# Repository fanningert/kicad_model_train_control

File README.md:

# Model Train Control

Control unit for analog model trains, based on ESPHome. A Home Assistant instance is used for visualization and control. This board is stackable up to 64 boards and every board has 16 outputs (3 pin). The Voltage is limited on the outputs per ESPHome template.
It comes in three variants, but all variants are the same boards. Only some components are not placed.

* Primary node with ESP32-S3-Wroom-2
* Primary node with ESP32-Devkit (can also be used as sub node with 3,3V power supply and protection)
* Sub node

## Features

* 16 h-bridges per board and stackable to 64 boards
* Reverse Voltage, Over Voltage and Under Voltage protection
* (optional) ESP32-Devkit
* (optional) ESP32-S3-Wroom-2

## Simple graphic of the board connections

```mermaid
flowchart LR
    Z[PowerSupply] ===|24V DC| A
    A[PCB_Core1] ===|24V DC, 3.3V, I2C| B & C & D
    B[PCB_Core2]
    C[PCB_Core...]
    D[PCB_Core64]
```

## Supported szenarios

- Power line
- Yield
- Generic Switch
- Signal
- Uncoupler

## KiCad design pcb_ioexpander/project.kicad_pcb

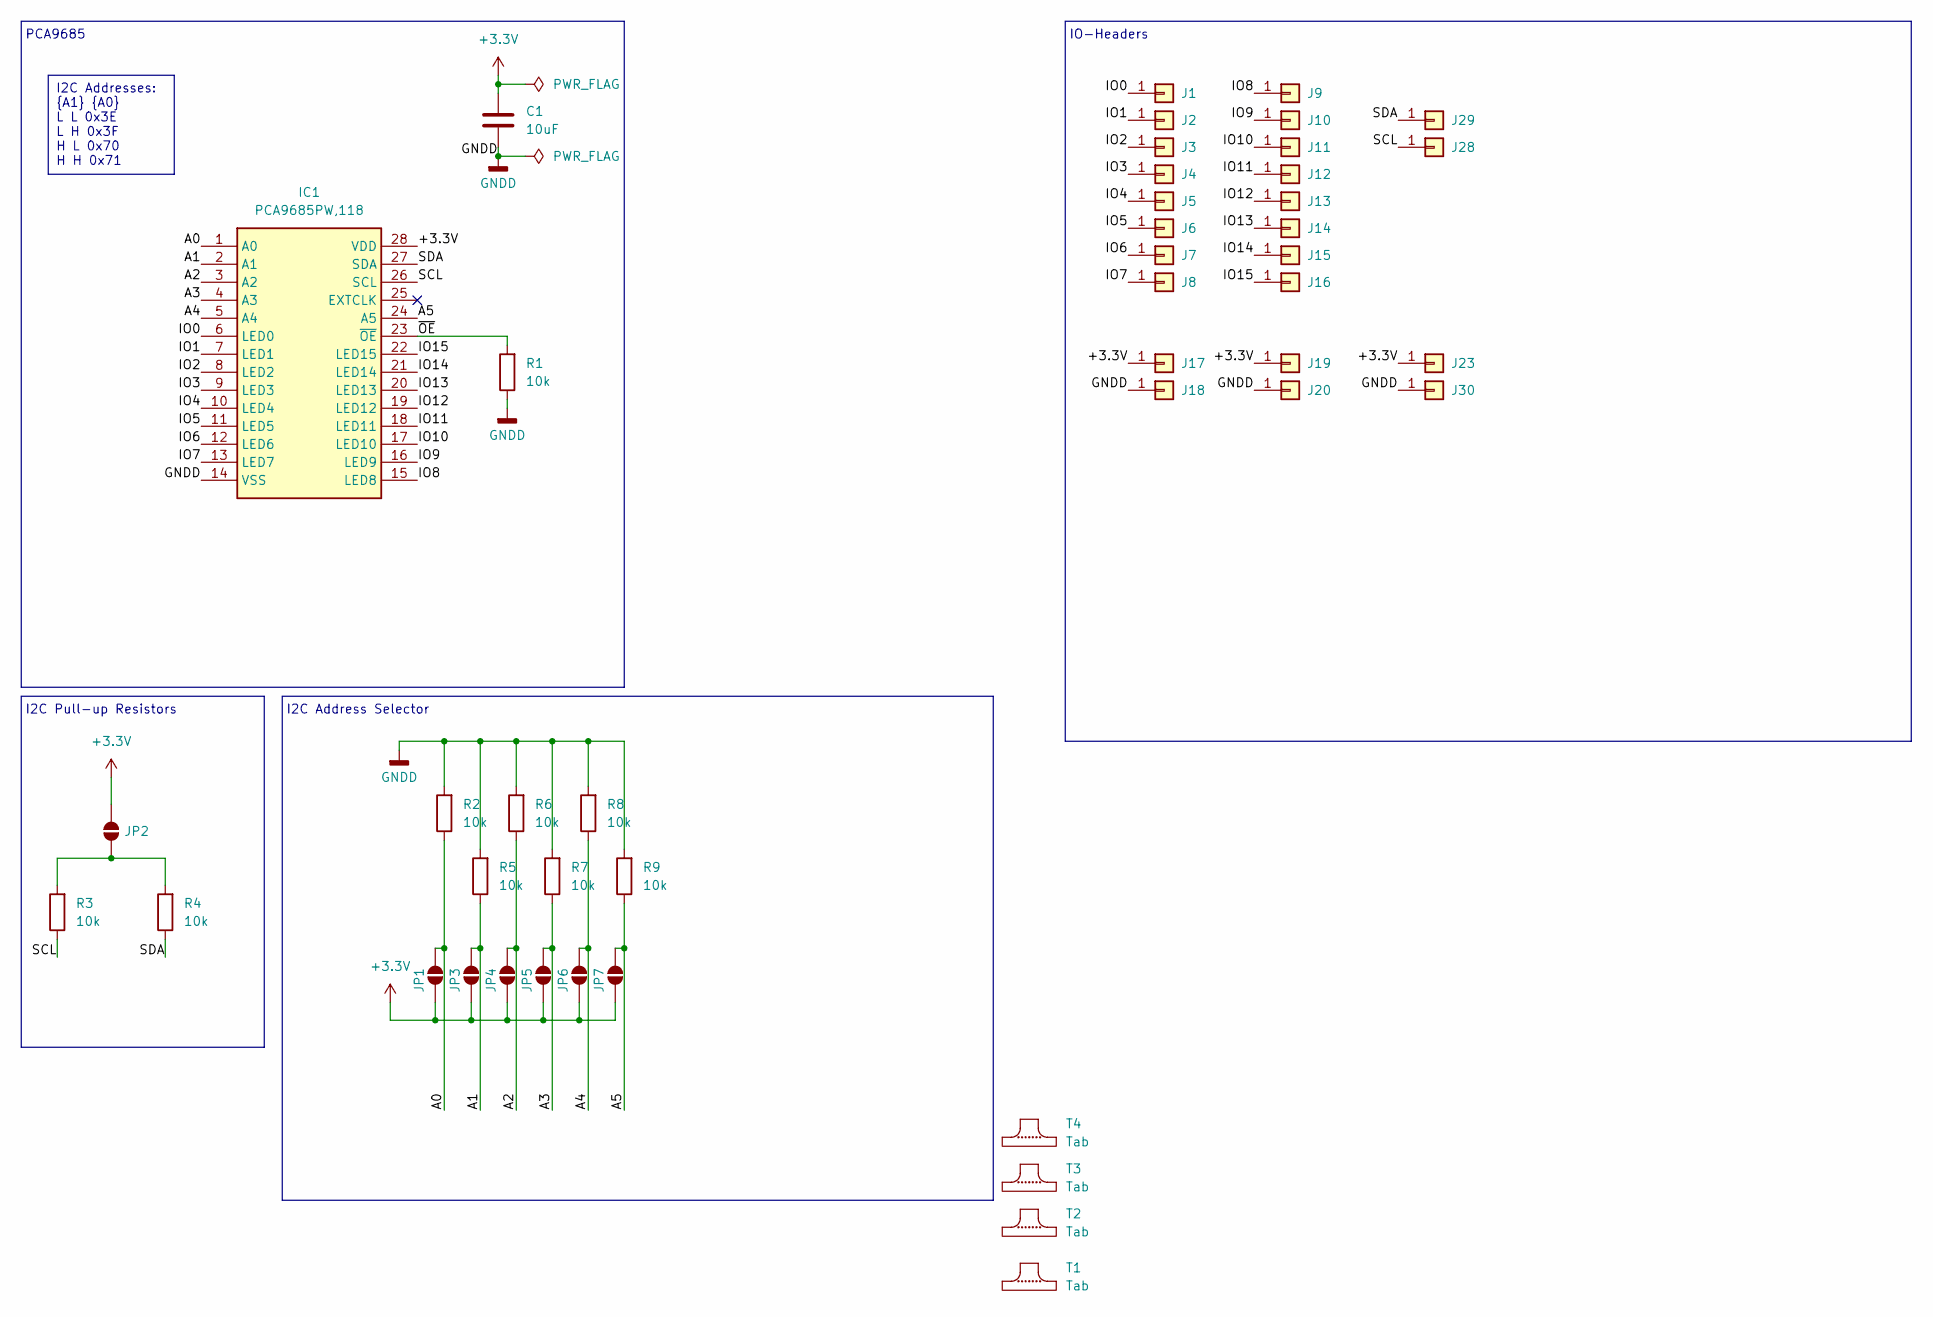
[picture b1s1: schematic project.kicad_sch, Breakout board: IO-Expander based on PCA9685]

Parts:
C1: 10uF; C_0402_1005Metric_Pad0.74x0.62mm_HandSolder
IC1: PCA9685PW,118; SOP65P640X110-28N; Mouser Part Number 771-PCA9685PW,118
J1, J2, J3, J4, J5, J6, J7, J8, J9, J10, J11, J12, J13, J14, J15, J16, J17, J18, J19, J20, J23, J28, J29, J30: Castellated_Hole02
JP1, JP2, JP3, JP4, JP5, JP6, JP7: SolderJumper_2_Open; SolderJumper-2_P1.3mm_Open_TrianglePad1.0x1.5mm
R1, R2, R3, R4, R5, R6, R7, R8, R9: 10k; R_0402_1005Metric_Pad0.72x0.64mm_HandSolder
T1, T2, T3, T4: Tab

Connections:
+3.3V: C1.1, IC1.28 (VDD), J17.1, J19.1, J23.1, JP1.2 (B), JP2.2 (B), JP3.2 (B), JP4.2 (B), JP5.2 (B), JP6.2 (B), JP7.2 (B)
/A0: IC1.1 (A0), JP1.1 (A), R2.1
/A1: IC1.2 (A1), JP3.1 (A), R5.1
/A2: IC1.3 (A2), JP4.1 (A), R6.1
/A3: IC1.4 (A3), JP5.1 (A), R7.1
/A4: IC1.5 (A4), JP6.1 (A), R8.1
/A5: IC1.24 (A5), JP7.1 (A), R9.1
/IO0: IC1.6 (LED0), J1.1
/IO1: IC1.7 (LED1), J2.1
/IO2: IC1.8 (LED2), J3.1
/IO3: IC1.9 (LED3), J4.1
/IO4: IC1.10 (LED4), J5.1
/IO5: IC1.11 (LED5), J6.1
/IO6: IC1.12 (LED6), J7.1
/IO7: IC1.13 (LED7), J8.1
/IO8: IC1.15 (LED8), J9.1
/IO9: IC1.16 (LED9), J10.1
/IO10: IC1.17 (LED10), J11.1
/IO11: IC1.18 (LED11), J12.1
/IO12: IC1.19 (LED12), J13.1
/IO13: IC1.20 (LED13), J14.1
/IO14: IC1.21 (LED14), J15.1
/IO15: IC1.22 (LED15), J16.1
/SCL: IC1.26 (SCL), J28.1, R3.1
/SDA: IC1.27 (SDA), J29.1, R4.1
/~OE: IC1.23 (~OE), R1.2
GNDD: C1.2, IC1.14 (VSS), J18.1, J20.1, J30.1, R1.1, R2.2, R5.2, R6.2, R7.2, R8.2, R9.2
unnamed: JP2.1 (A), R3.2, R4.2

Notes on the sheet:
I2C Addresses: {A1} {A0} L L 0x3E L H 0x3F H L 0x70 H H 0x71
IO-Headers
I2C Address Selector
I2C Pull-up Resistors
PCA9685

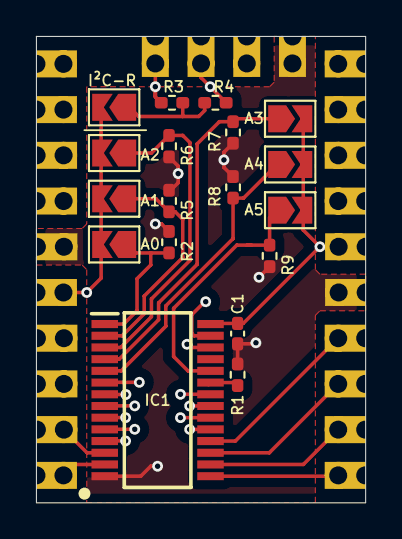
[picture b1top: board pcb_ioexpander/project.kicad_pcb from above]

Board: 4 copper layers, 18.3 x 25.9 mm, 47 parts (1 on the bottom side), 28 nets.

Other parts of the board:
QR*****: https://github.com/fanningert/kicad_pcb_ioexpander; //github.com/fanningert/kicad_pcb_ioexpander

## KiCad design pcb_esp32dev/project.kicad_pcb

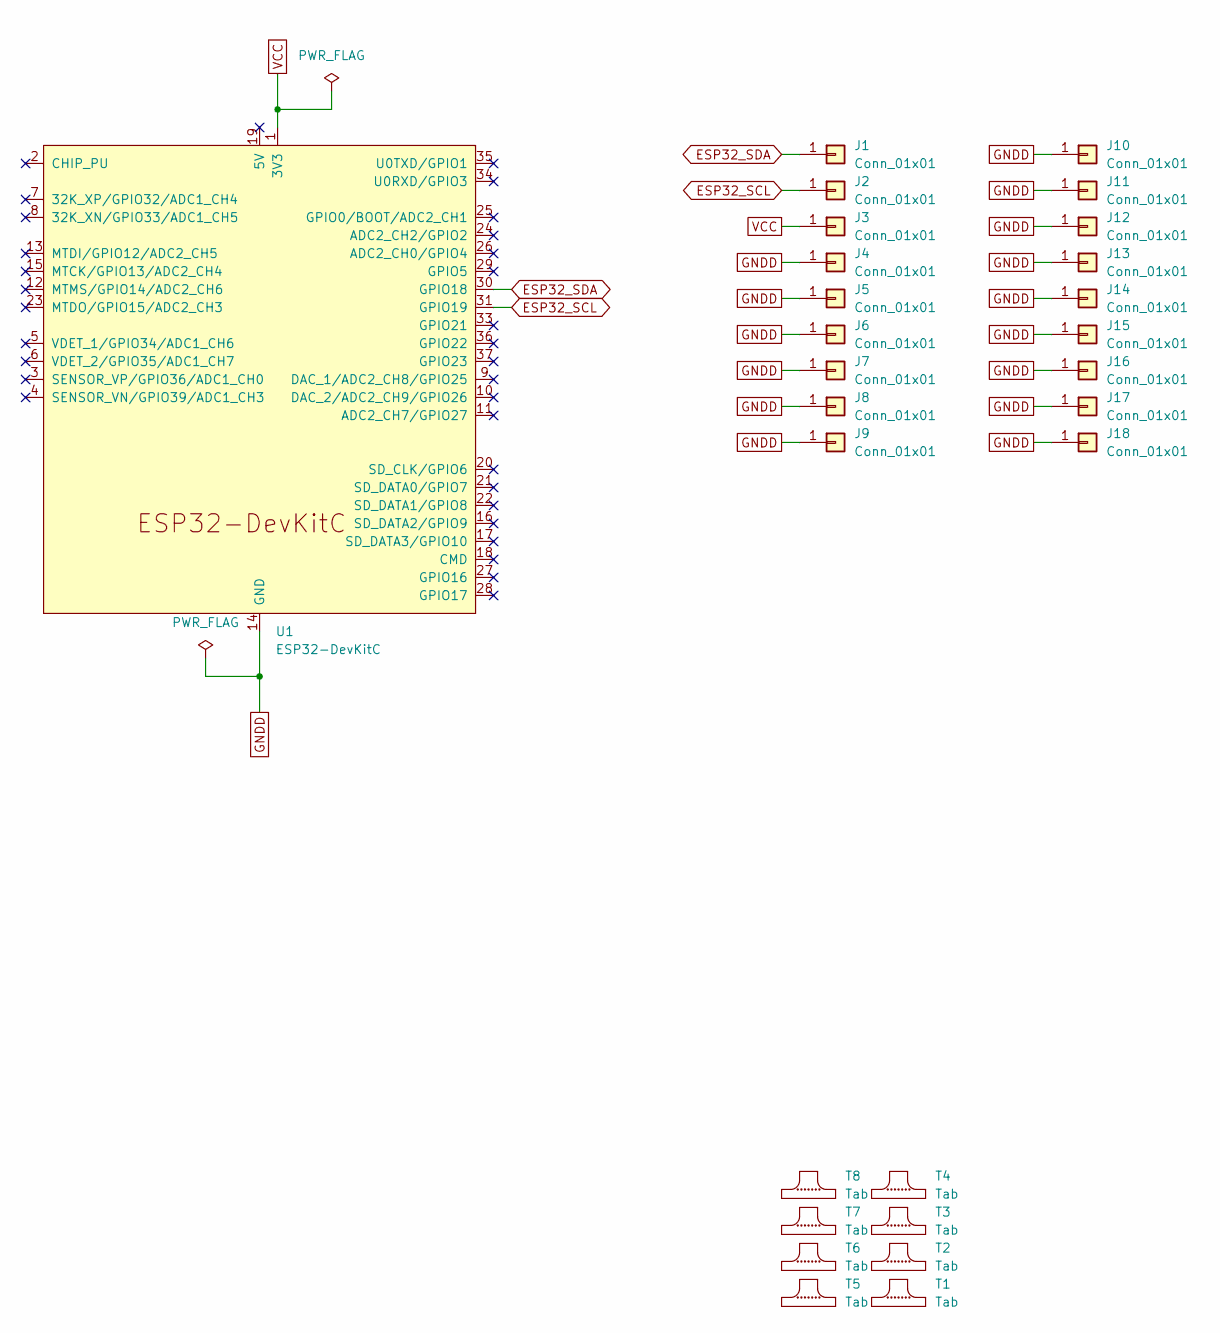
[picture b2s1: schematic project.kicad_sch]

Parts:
J1, J2, J3, J4, J5, J6, J7, J8, J9, J10, J11, J12, J13, J14, J15, J16, J17, J18: Conn_01x01; Castellated_Hole02
T1, T2, T3, T4, T5, T6, T7, T8: Tab
U1: ESP32-DevKitC

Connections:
ESP32_SCL: J2.1, U1.31 (GPIO19)
ESP32_SDA: J1.1, U1.30 (GPIO18)
GNDD: J4.1, J5.1, J6.1, J7.1, J8.1, J9.1, J10.1, J11.1, J12.1, J13.1, J14.1, J15.1, J16.1, J17.1, J18.1, U1.14 (GND), U1.32 (GND), U1.38 (GND)
VCC: J3.1, U1.1 (3V3)

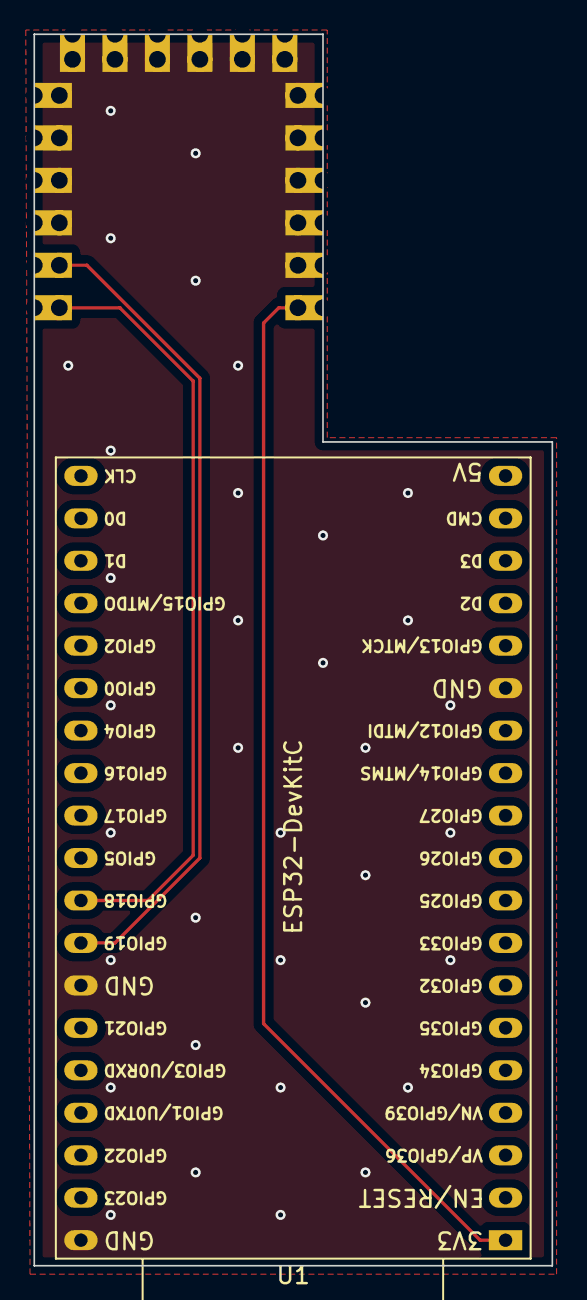
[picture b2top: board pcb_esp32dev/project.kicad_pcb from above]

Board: 2 copper layers, 31.0 x 73.7 mm, 27 parts (0 on the bottom side), 4 nets.

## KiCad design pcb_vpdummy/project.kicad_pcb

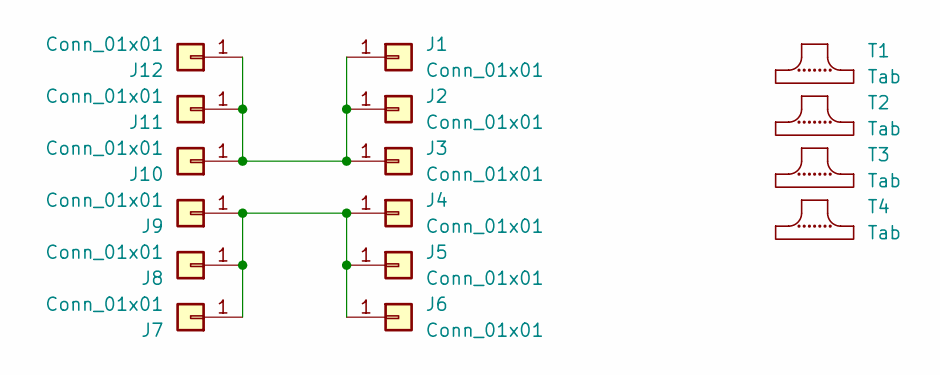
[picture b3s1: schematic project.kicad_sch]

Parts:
J1, J2, J3, J4, J5, J6, J7, J8, J9, J10, J11, J12: Conn_01x01; Castellated_Hole02
T1, T2, T3, T4: Tab

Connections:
unnamed: J1.1, J2.1, J3.1, J10.1, J11.1, J12.1
unnamed: J4.1, J5.1, J6.1, J7.1, J8.1, J9.1

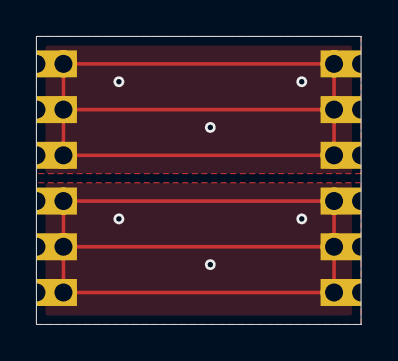
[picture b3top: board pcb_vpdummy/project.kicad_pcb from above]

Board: 2 copper layers, 18.0 x 16.0 mm, 16 parts (0 on the bottom side), 2 nets.

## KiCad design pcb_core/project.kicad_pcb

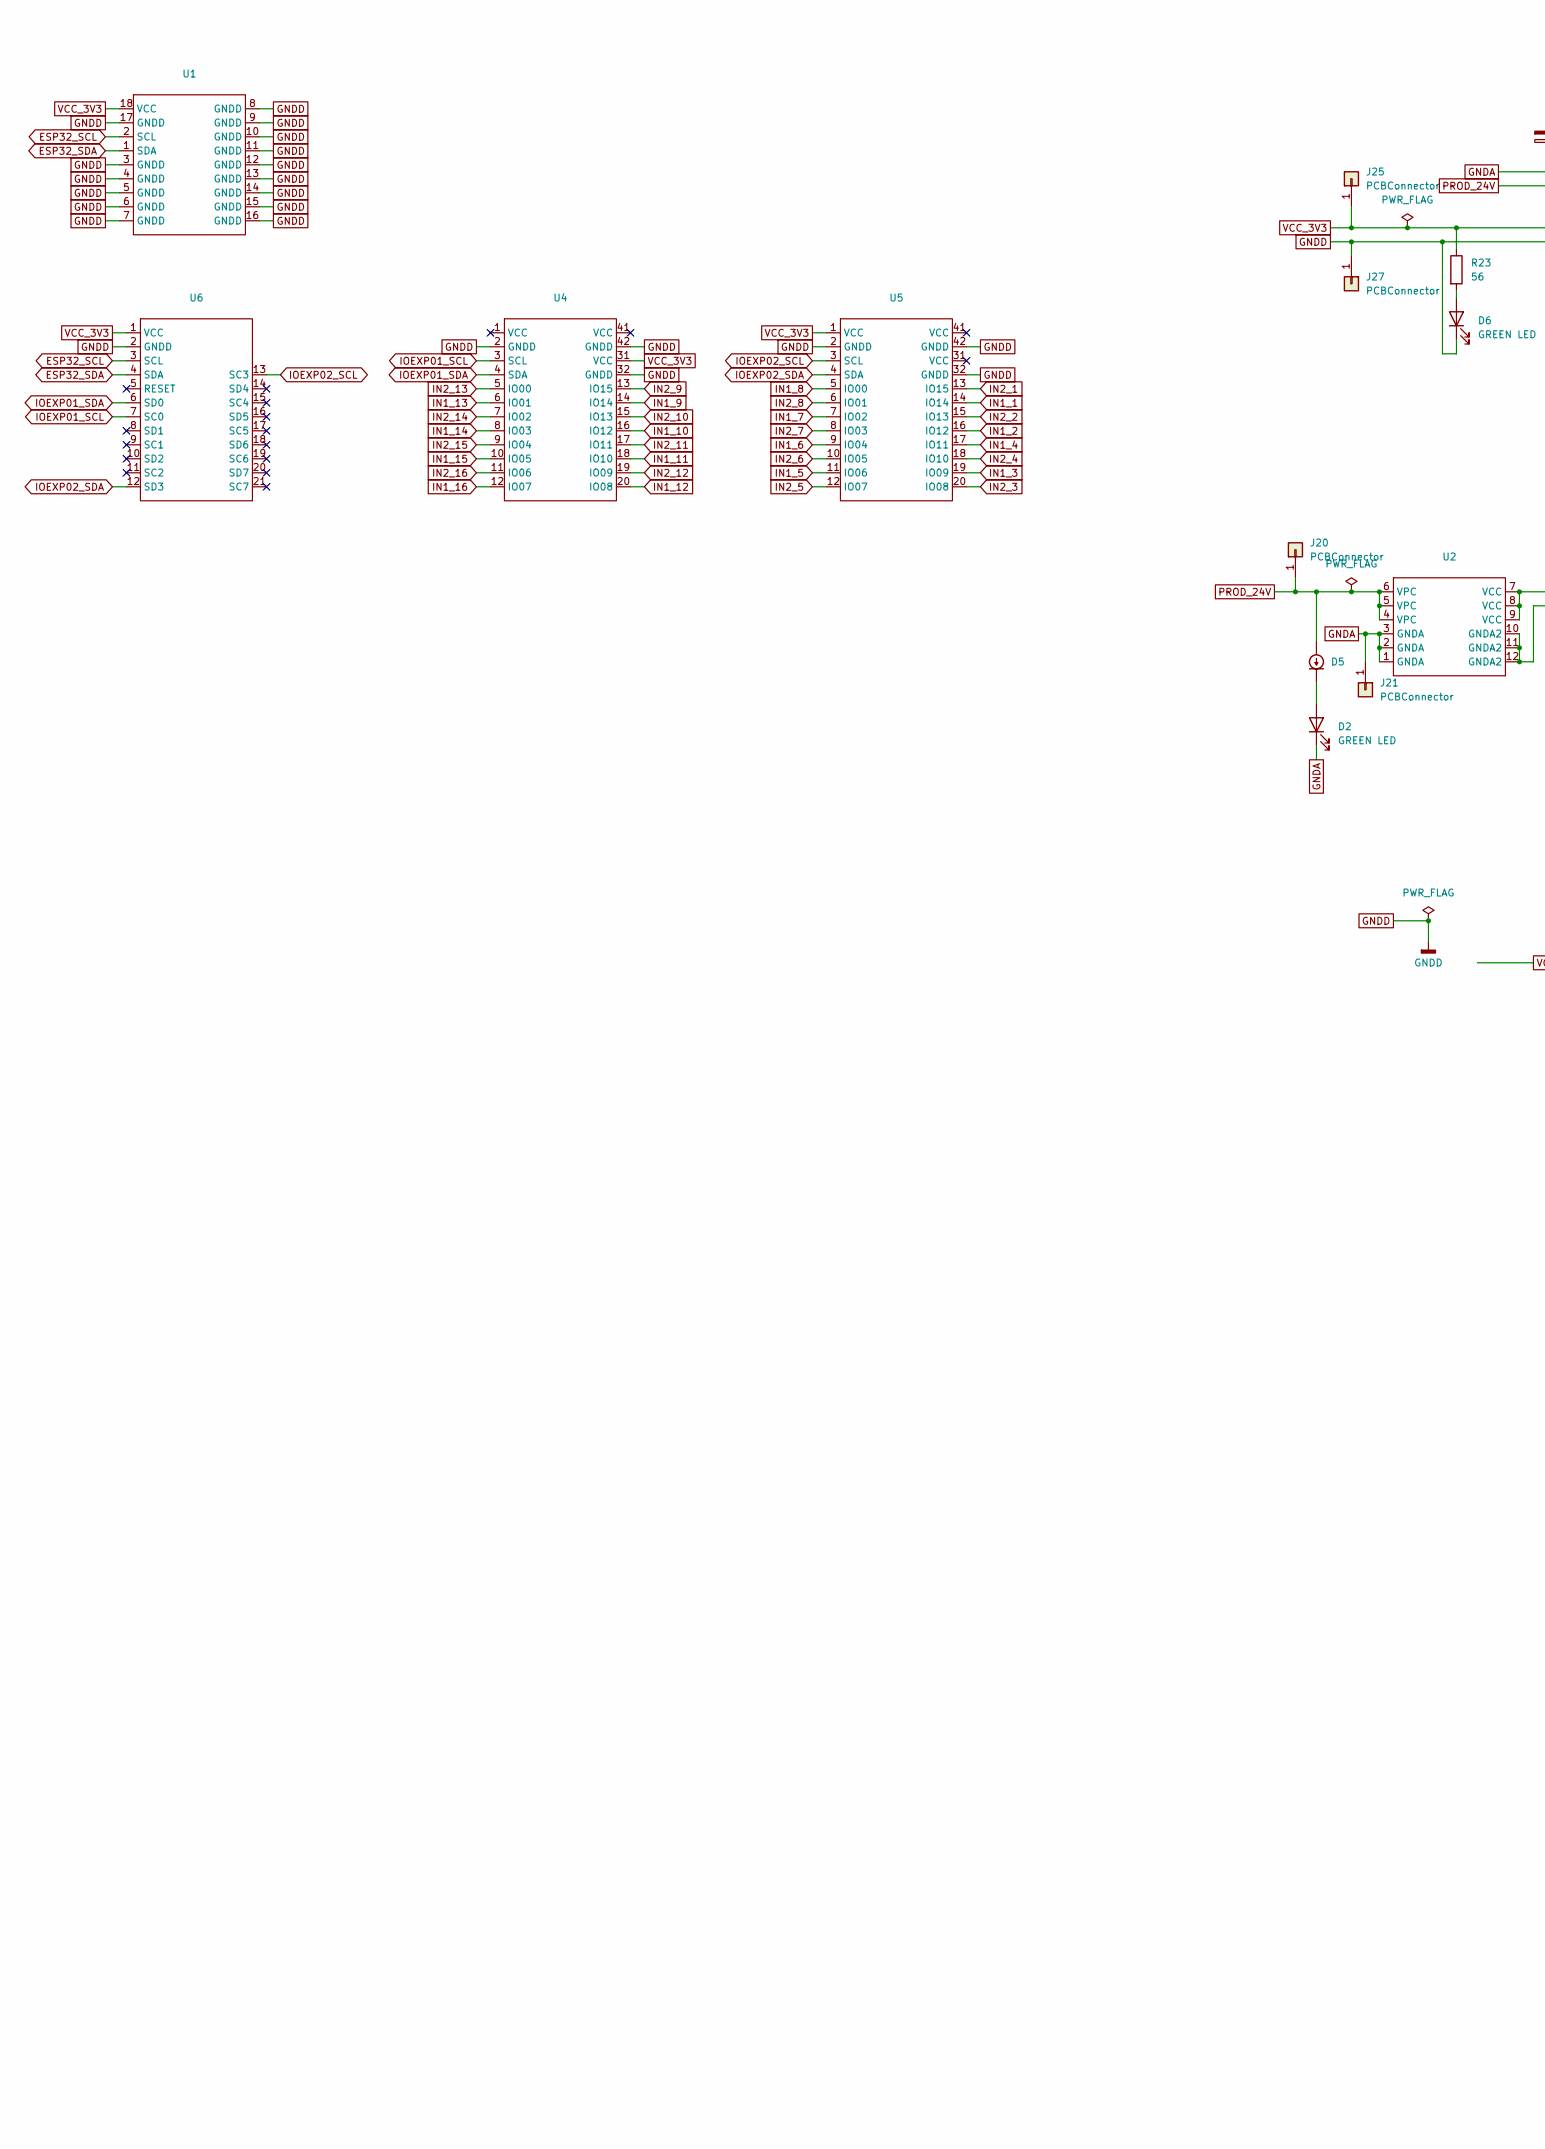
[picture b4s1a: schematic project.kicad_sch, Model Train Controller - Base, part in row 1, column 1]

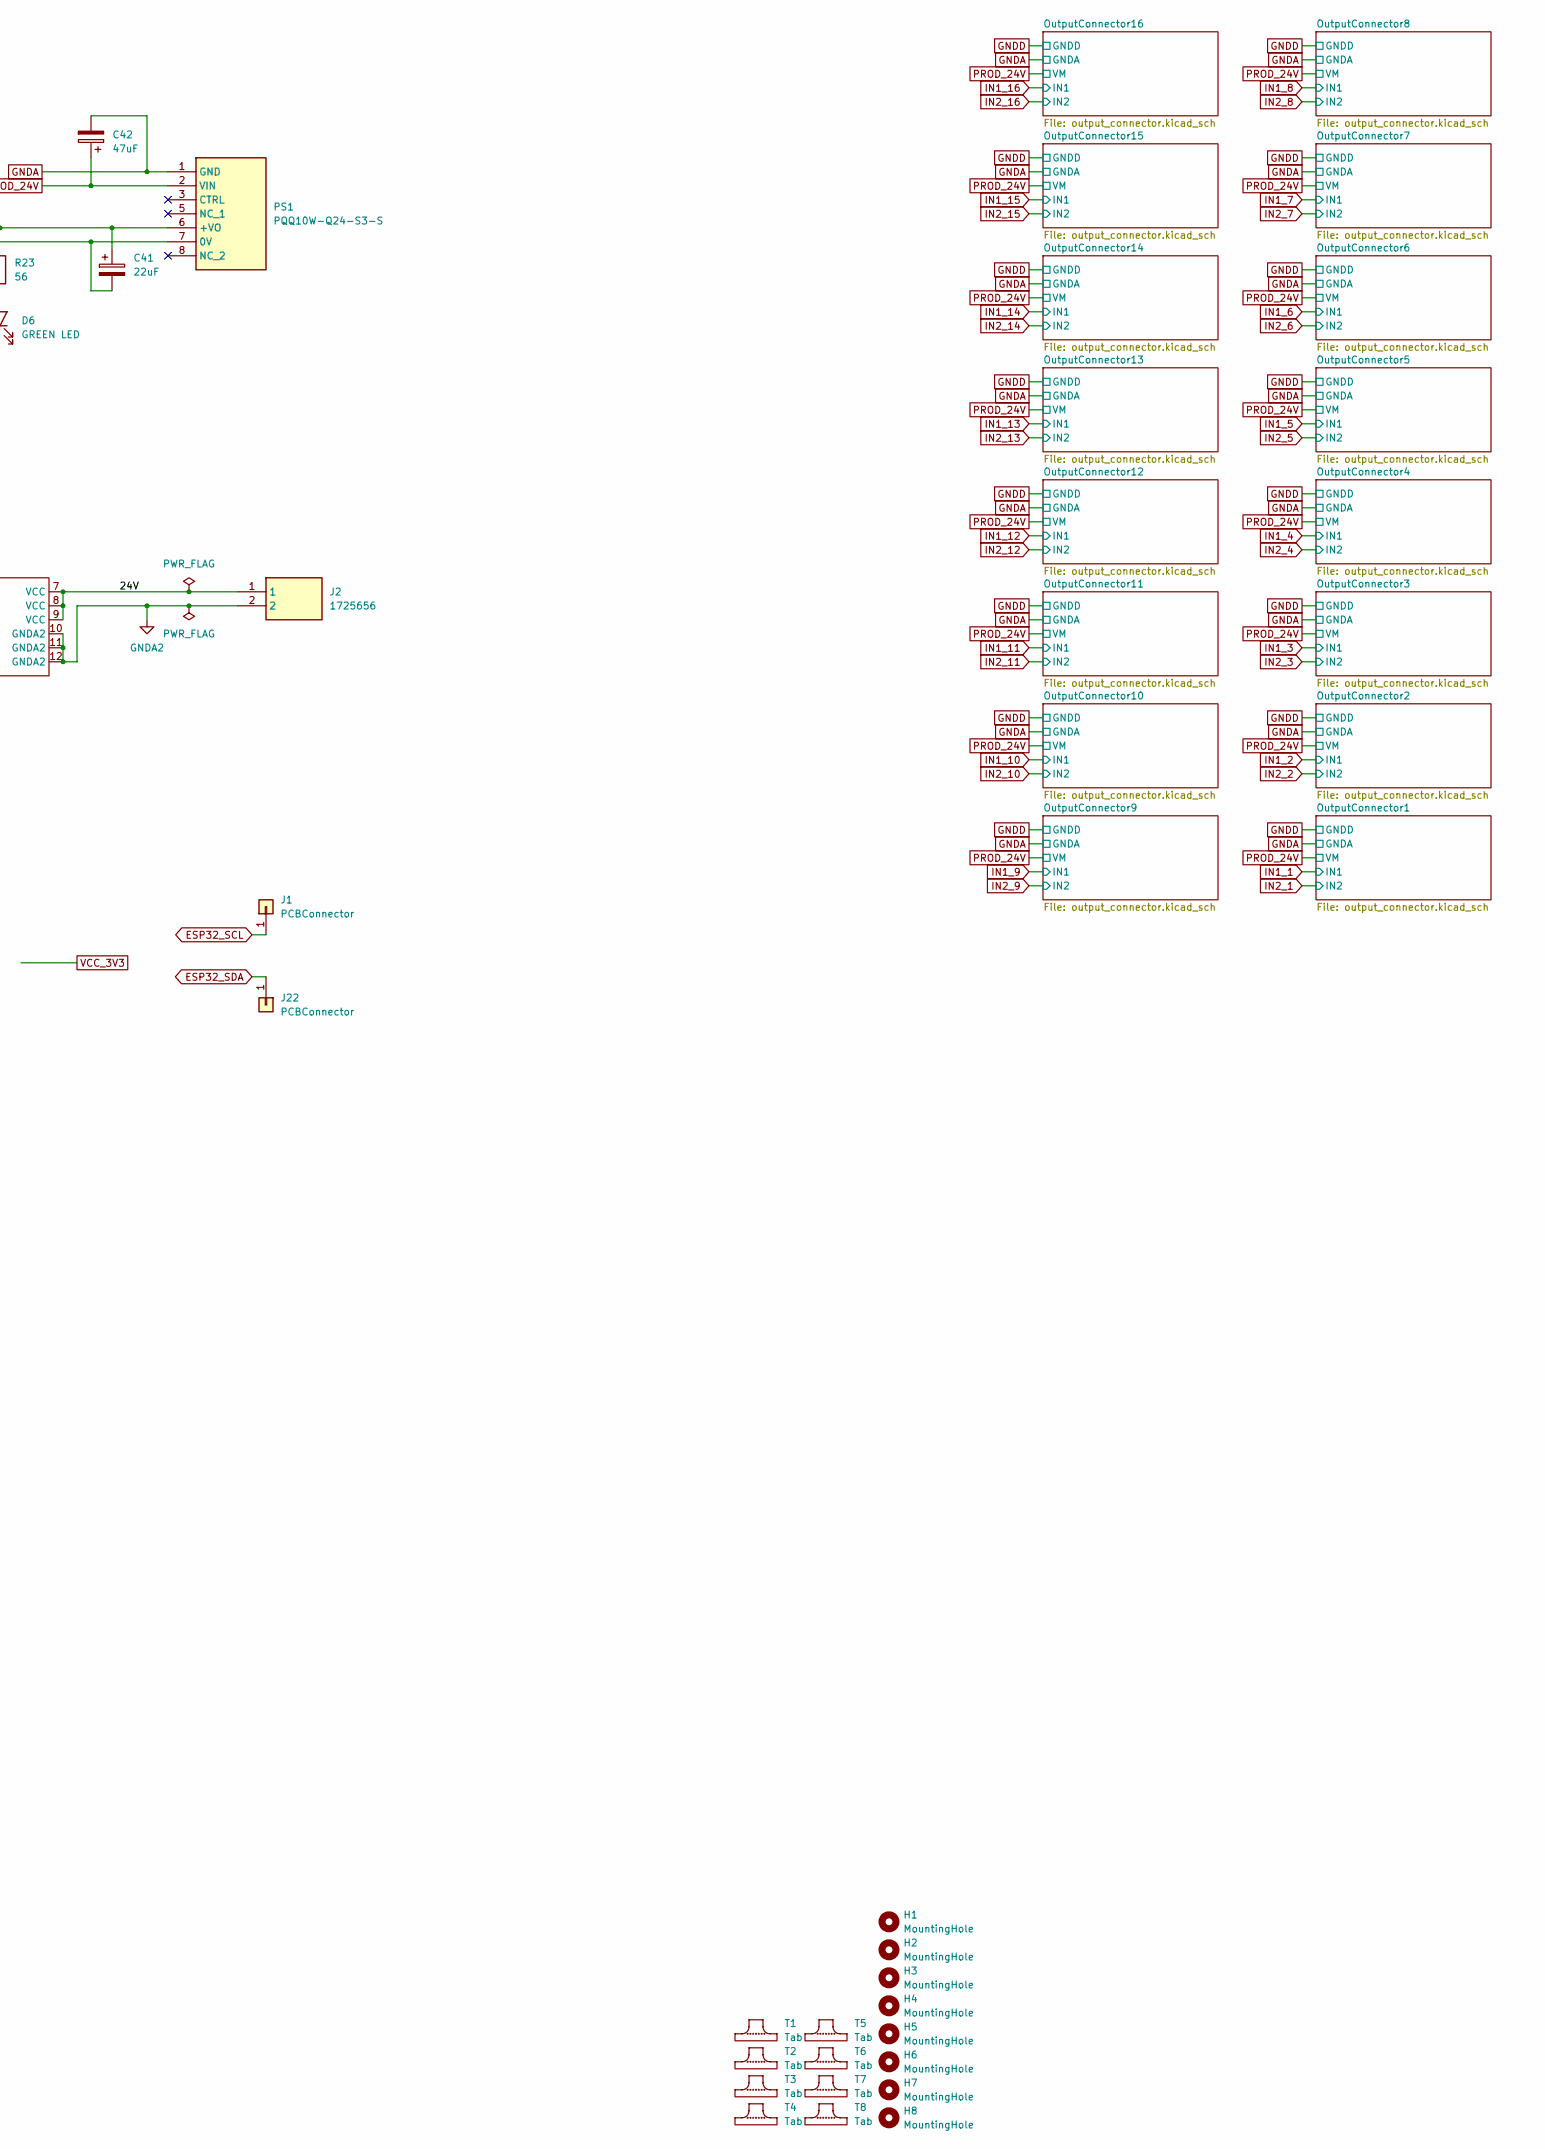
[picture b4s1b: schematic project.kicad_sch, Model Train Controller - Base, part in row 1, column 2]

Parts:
C41: 22uF; CP_Elec_6.3x7.7; Manufacturer_Part_Number Polarized Capacitor, 22.0uF, 63V, D6.3x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; LCSC# C5246567
C42: 47uF; CP_Elec_6.3x7.7; Manufacturer_Part_Number FZ47UF35V90RV0124; LCSC# C267471
D2, D6: GREEN LED; LED_1206_3216Metric_Pad1.42x1.75mm_HandSolder; Manufacturer_Part_Number SML-012P8TT86; LCSC# C5336737
D5: D_SOD-123F; Manufacturer_Part_Number CMJ2000 TR PBFREE; Mouser Part Number 610-CMJ2000TR
H1, H2, H3, H4, H5, H6, H7, H8: MountingHole; MountingHole_3.2mm_M3_Pad_Via
J1, J20, J21, J22, J25, J27: PCBConnector; TestPoint_THTPad_D3.0mm_Drill1.5mm
J2: 1725656; Mouser Part Number 651-1725656
PS1: PQQ10W-Q24-S3-S; PQQ10WQ24S3S; Mouser Part Number 490-PQQ10W-Q24-S3-S
R23: 56; R_1206_3216Metric_Pad1.30x1.75mm_HandSolder; Mouser Part Number 71-CRCW1206-56-E3; LCSC# C2933788
T1, T2, T3, T4, T5, T6, T7, T8: Tab
U1: esp32
U2: voltage_protection
U4, U5: ioexpander
U6: i2cmultiplexer

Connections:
/24V: J2.1, U2.7 (VCC), U2.8 (VCC), U2.9 (VCC)
ESP32_SCL: J1.1, U1.2 (SCL), U6.3 (SCL)
ESP32_SDA: J22.1, U1.1 (SDA), U6.4 (SDA)
GNDA: C42.2, D2.1 (K), J21.1, PS1.1 (GND), U2.1 (GNDA), U2.2 (GNDA), U2.3 (GNDA); also elsewhere on the board
GNDA2: J2.2, U2.10 (GNDA2), U2.11 (GNDA2), U2.12 (GNDA2)
GNDD: C41.2, D6.1 (K), J27.1, PS1.7 (0V), U1.3 (GNDD), U1.4 (GNDD), U1.5 (GNDD), U1.6 (GNDD), U1.7 (GNDD), U1.8 (GNDD), U1.9 (GNDD), U1.10 (GNDD), U1.11 (GNDD), U1.12 (GNDD), U1.13 (GNDD), U1.14 (GNDD), U1.15 (GNDD), U1.16 (GNDD), U1.17 (GNDD), U4.2 (GNDD), U4.32 (GNDD), U4.42 (GNDD), U5.2 (GNDD), U5.32 (GNDD), U5.42 (GNDD), U6.2 (GNDD); also elsewhere on the board
IN1_1: U5.14 (IO14); also elsewhere on the board
IN1_2: U5.16 (IO12); also elsewhere on the board
IN1_3: U5.19 (IO09); also elsewhere on the board
IN1_4: U5.17 (IO11); also elsewhere on the board
IN1_5: U5.11 (IO06); also elsewhere on the board
IN1_6: U5.9 (IO04); also elsewhere on the board
IN1_7: U5.7 (IO02); also elsewhere on the board
IN1_8: U5.5 (IO00); also elsewhere on the board
IN1_9: U4.14 (IO14); also elsewhere on the board
IN1_10: U4.16 (IO12); also elsewhere on the board
IN1_11: U4.18 (IO10); also elsewhere on the board
IN1_12: U4.20 (IO08); also elsewhere on the board
IN1_13: U4.6 (IO01); also elsewhere on the board
IN1_14: U4.8 (IO03); also elsewhere on the board
IN1_15: U4.10 (IO05); also elsewhere on the board
IN1_16: U4.12 (IO07); also elsewhere on the board
IN2_1: U5.13 (IO15); also elsewhere on the board
IN2_2: U5.15 (IO13); also elsewhere on the board
IN2_3: U5.20 (IO08); also elsewhere on the board
IN2_4: U5.18 (IO10); also elsewhere on the board
IN2_5: U5.12 (IO07); also elsewhere on the board
IN2_6: U5.10 (IO05); also elsewhere on the board
IN2_7: U5.8 (IO03); also elsewhere on the board
IN2_8: U5.6 (IO01); also elsewhere on the board
IN2_9: U4.13 (IO15); also elsewhere on the board
IN2_10: U4.15 (IO13); also elsewhere on the board
IN2_11: U4.17 (IO11); also elsewhere on the board
IN2_12: U4.19 (IO09); also elsewhere on the board
IN2_13: U4.5 (IO00); also elsewhere on the board
IN2_14: U4.7 (IO02); also elsewhere on the board
IN2_15: U4.9 (IO04); also elsewhere on the board
IN2_16: U4.11 (IO06); also elsewhere on the board
IOEXP01_SCL: U4.3 (SCL), U6.7 (SC0)
IOEXP01_SDA: U4.4 (SDA), U6.6 (SD0)
IOEXP02_SCL: U5.3 (SCL), U6.13 (SC3)
IOEXP02_SDA: U5.4 (SDA), U6.12 (SD3)
unnamed: D2.2 (A), D5.1 (K)
unnamed: D6.2 (A), R23.2
PROD_24V: C42.1, D5.2 (A), J20.1, PS1.2 (VIN), U2.4 (VPC), U2.5 (VPC), U2.6 (VPC); also elsewhere on the board
VCC_3V3: C41.1, J25.1, PS1.6 (+VO), R23.1, U1.18 (VCC), U4.31 (VCC), U5.1 (VCC), U6.1 (VCC)

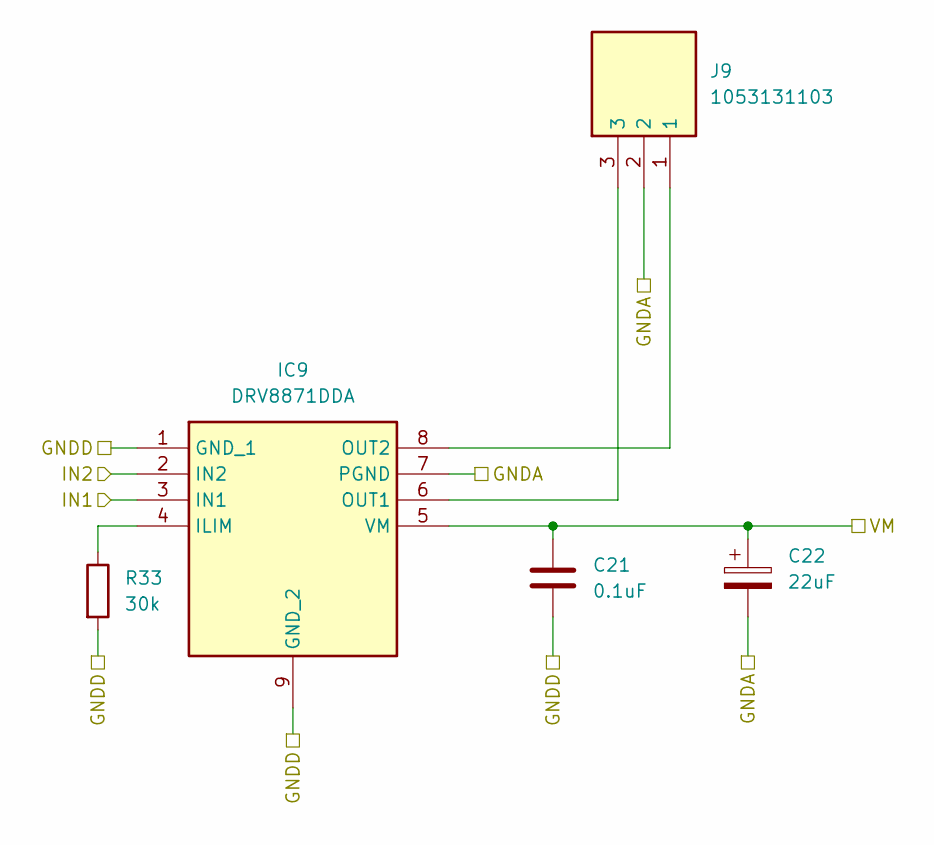
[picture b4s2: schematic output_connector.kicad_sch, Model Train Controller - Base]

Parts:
C21: 0.1uF; C_0805_2012Metric_Pad1.18x1.45mm_HandSolder; Manufacturer_Part_Number Capacitor, 0.1uF, 50V, 0805 SMD; LCSC# C49678
C22: 22uF; CP_Elec_6.3x7.7; Manufacturer_Part_Number Polarized Capacitor, 22.0uF, 63V, D6.3x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; LCSC# C5246567
IC9: DRV8871DDA; SOIC127P600X170-9N; Manufacturer_Part_Number DRV8871DDA; LCSC# C1556867
J9: 1053131103; 105313YY03; Manufacturer_Part_Number 1053131103; Mouser Part Number 538-105313-1103
R33: 30k; R_1206_3216Metric_Pad1.30x1.75mm_HandSolder; Mouser Part Number 652-CR1206FX-3002ELF; LCSC# C2907479

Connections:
GNDA: C22.2, IC9.7 (PGND), J9.2; also elsewhere on the board
GNDD: C21.2, IC9.1 (GND_1), IC9.9 (GND_2), R33.2; also elsewhere on the board
IN1_7: IC9.3 (IN1); also elsewhere on the board
IN2_7: IC9.2 (IN2); also elsewhere on the board
unnamed: IC9.4 (ILIM), R33.1
unnamed: IC9.6 (OUT1), J9.3
unnamed: IC9.8 (OUT2), J9.1
PROD_24V: C21.1, C22.1, IC9.5 (VM); also elsewhere on the board

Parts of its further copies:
C6, C10, C13, C15, C17, C19, C23, C25, C27, C29, C31, C33, C35, C37, C39: 0.1uF; C_0805_2012Metric_Pad1.18x1.45mm_HandSolder; Manufacturer_Part_Number Capacitor, 0.1uF, 50V, 0805 SMD; LCSC# C49678
C7, C12, C14, C16, C18, C20, C24, C26, C28, C30, C32, C34, C36, C38, C40: 22uF; CP_Elec_6.3x7.7; Manufacturer_Part_Number Polarized Capacitor, 22.0uF, 63V, D6.3x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; LCSC# C5246567
IC1, IC3, IC5, IC6, IC7, IC8, IC10, IC11, IC12, IC13, IC14, IC15, IC16, IC17, IC18: DRV8871DDA; SOIC127P600X170-9N; Manufacturer_Part_Number DRV8871DDA; LCSC# C1556867
J3, J4, J5, J6, J7, J8, J10, J11, J12, J13, J14, J15, J16, J17, J18: 1053131103; 105313YY03; Manufacturer_Part_Number 1053131103; Mouser Part Number 538-105313-1103
R8, R18, R21, R24, R27, R30, R36, R39, R42, R45, R48, R51, R54, R57, R60: 30k; R_1206_3216Metric_Pad1.30x1.75mm_HandSolder; Mouser Part Number 652-CR1206FX-3002ELF; LCSC# C2907479

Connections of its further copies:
GNDA: C7.2, C12.2, C14.2, C16.2, C18.2, C20.2, C24.2, C26.2, C28.2, C30.2, C32.2, C34.2, C36.2, C38.2, C40.2, IC1.7 (PGND), IC3.7 (PGND), IC5.7 (PGND), IC6.7 (PGND), IC7.7 (PGND), IC8.7 (PGND), IC10.7 (PGND), IC11.7 (PGND), IC12.7 (PGND), IC13.7 (PGND), IC14.7 (PGND), IC15.7 (PGND), IC16.7 (PGND), IC17.7 (PGND), IC18.7 (PGND), J3.2, J4.2, J5.2, J6.2, J7.2, J8.2, J10.2, J11.2, J12.2, J13.2, J14.2, J15.2, J16.2, J17.2, J18.2; also elsewhere on the board
GNDD: C6.2, C10.2, C13.2, C15.2, C17.2, C19.2, C23.2, C25.2, C27.2, C29.2, C31.2, C33.2, C35.2, C37.2, C39.2, IC1.1 (GND_1), IC1.9 (GND_2), IC3.1 (GND_1), IC3.9 (GND_2), IC5.1 (GND_1), IC5.9 (GND_2), IC6.1 (GND_1), IC6.9 (GND_2), IC7.1 (GND_1), IC7.9 (GND_2), IC8.1 (GND_1), IC8.9 (GND_2), IC10.1 (GND_1), IC10.9 (GND_2), IC11.1 (GND_1), IC11.9 (GND_2), IC12.1 (GND_1), IC12.9 (GND_2), IC13.1 (GND_1), IC13.9 (GND_2), IC14.1 (GND_1), IC14.9 (GND_2), IC15.1 (GND_1), IC15.9 (GND_2), IC16.1 (GND_1), IC16.9 (GND_2), IC17.1 (GND_1), IC17.9 (GND_2), IC18.1 (GND_1), IC18.9 (GND_2), R8.2, R18.2, R21.2, R24.2, R27.2, R30.2, R36.2, R39.2, R42.2, R45.2, R48.2, R51.2, R54.2, R57.2, R60.2; also elsewhere on the board
IN1_1: IC1.3 (IN1); also elsewhere on the board
IN1_2: IC3.3 (IN1); also elsewhere on the board
IN1_3: IC5.3 (IN1); also elsewhere on the board
IN1_4: IC6.3 (IN1); also elsewhere on the board
IN1_5: IC7.3 (IN1); also elsewhere on the board
IN1_6: IC8.3 (IN1); also elsewhere on the board
IN1_8: IC10.3 (IN1); also elsewhere on the board
IN1_9: IC11.3 (IN1); also elsewhere on the board
IN1_10: IC12.3 (IN1); also elsewhere on the board
IN1_11: IC13.3 (IN1); also elsewhere on the board
IN1_12: IC14.3 (IN1); also elsewhere on the board
IN1_13: IC15.3 (IN1); also elsewhere on the board
IN1_14: IC16.3 (IN1); also elsewhere on the board
IN1_15: IC17.3 (IN1); also elsewhere on the board
IN1_16: IC18.3 (IN1); also elsewhere on the board
IN2_1: IC1.2 (IN2); also elsewhere on the board
IN2_2: IC3.2 (IN2); also elsewhere on the board
IN2_3: IC5.2 (IN2); also elsewhere on the board
IN2_4: IC6.2 (IN2); also elsewhere on the board
IN2_5: IC7.2 (IN2); also elsewhere on the board
IN2_6: IC8.2 (IN2); also elsewhere on the board
IN2_8: IC10.2 (IN2); also elsewhere on the board
IN2_9: IC11.2 (IN2); also elsewhere on the board
IN2_10: IC12.2 (IN2); also elsewhere on the board
IN2_11: IC13.2 (IN2); also elsewhere on the board
IN2_12: IC14.2 (IN2); also elsewhere on the board
IN2_13: IC15.2 (IN2); also elsewhere on the board
IN2_14: IC16.2 (IN2); also elsewhere on the board
IN2_15: IC17.2 (IN2); also elsewhere on the board
IN2_16: IC18.2 (IN2); also elsewhere on the board
unnamed: IC1.4 (ILIM), R8.1
unnamed: IC1.6 (OUT1), J3.3
unnamed: IC1.8 (OUT2), J3.1
unnamed: IC3.4 (ILIM), R18.1
unnamed: IC3.6 (OUT1), J4.3
unnamed: IC3.8 (OUT2), J4.1
unnamed: IC5.4 (ILIM), R21.1
unnamed: IC5.6 (OUT1), J5.3
unnamed: IC5.8 (OUT2), J5.1
unnamed: IC6.4 (ILIM), R24.1
unnamed: IC6.6 (OUT1), J6.3
unnamed: IC6.8 (OUT2), J6.1
unnamed: IC7.4 (ILIM), R27.1
unnamed: IC7.6 (OUT1), J7.3
unnamed: IC7.8 (OUT2), J7.1
unnamed: IC8.4 (ILIM), R30.1
unnamed: IC8.6 (OUT1), J8.3
unnamed: IC8.8 (OUT2), J8.1
unnamed: IC10.4 (ILIM), R36.1
unnamed: IC10.6 (OUT1), J10.3
unnamed: IC10.8 (OUT2), J10.1
unnamed: IC11.4 (ILIM), R39.1
unnamed: IC11.6 (OUT1), J11.3
unnamed: IC11.8 (OUT2), J11.1
unnamed: IC12.4 (ILIM), R42.1
unnamed: IC12.6 (OUT1), J12.3
unnamed: IC12.8 (OUT2), J12.1
unnamed: IC13.4 (ILIM), R45.1
unnamed: IC13.6 (OUT1), J13.3
unnamed: IC13.8 (OUT2), J13.1
unnamed: IC14.4 (ILIM), R48.1
unnamed: IC14.6 (OUT1), J14.3
unnamed: IC14.8 (OUT2), J14.1
unnamed: IC15.4 (ILIM), R51.1
unnamed: IC15.6 (OUT1), J15.3
unnamed: IC15.8 (OUT2), J15.1
unnamed: IC16.4 (ILIM), R54.1
unnamed: IC16.6 (OUT1), J16.3
unnamed: IC16.8 (OUT2), J16.1
unnamed: IC17.4 (ILIM), R57.1
unnamed: IC17.6 (OUT1), J17.3
unnamed: IC17.8 (OUT2), J17.1
unnamed: IC18.4 (ILIM), R60.1
unnamed: IC18.6 (OUT1), J18.3
unnamed: IC18.8 (OUT2), J18.1
PROD_24V: C6.1, C7.1, C10.1, C12.1, C13.1, C14.1, C15.1, C16.1, C17.1, C18.1, C19.1, C20.1, C23.1, C24.1, C25.1, C26.1, C27.1, C28.1, C29.1, C30.1, C31.1, C32.1, C33.1, C34.1, C35.1, C36.1, C37.1, C38.1, C39.1, C40.1, IC1.5 (VM), IC3.5 (VM), IC5.5 (VM), IC6.5 (VM), IC7.5 (VM), IC8.5 (VM), IC10.5 (VM), IC11.5 (VM), IC12.5 (VM), IC13.5 (VM), IC14.5 (VM), IC15.5 (VM), IC16.5 (VM), IC17.5 (VM), IC18.5 (VM); also elsewhere on the board

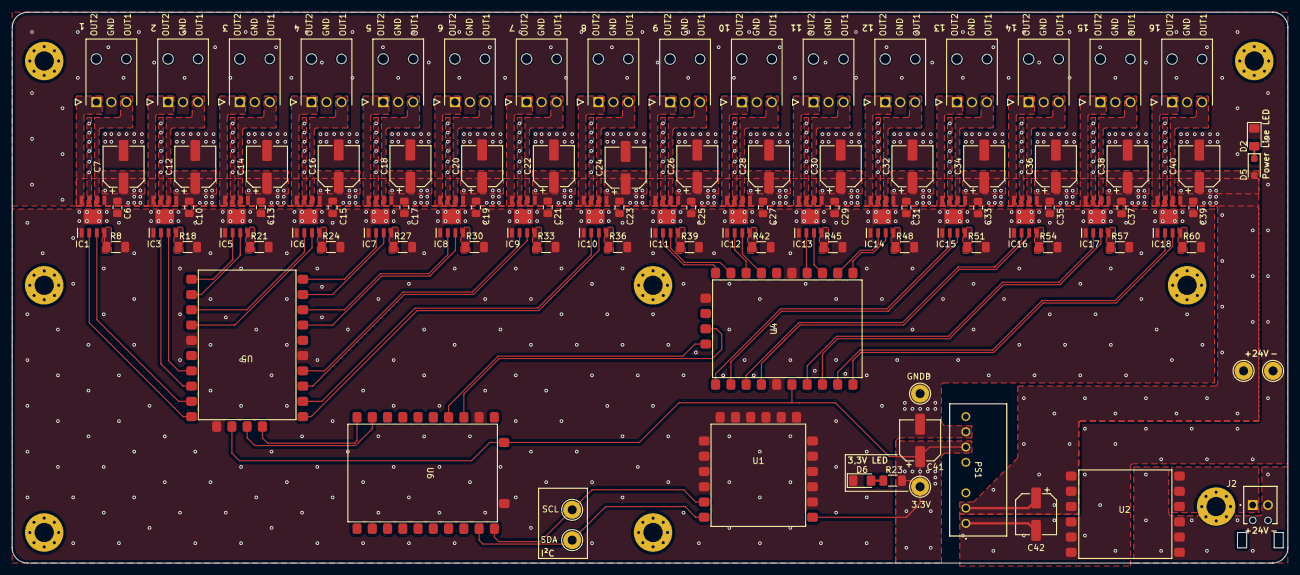
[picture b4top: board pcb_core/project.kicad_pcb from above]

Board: 2 copper layers, 212.3 x 91.7 mm, 115 parts (0 on the bottom side), 94 nets.
